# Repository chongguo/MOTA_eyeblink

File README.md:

# MOTA_eyeblink
Here are the design files and code for a custom eye blink conditioning system.

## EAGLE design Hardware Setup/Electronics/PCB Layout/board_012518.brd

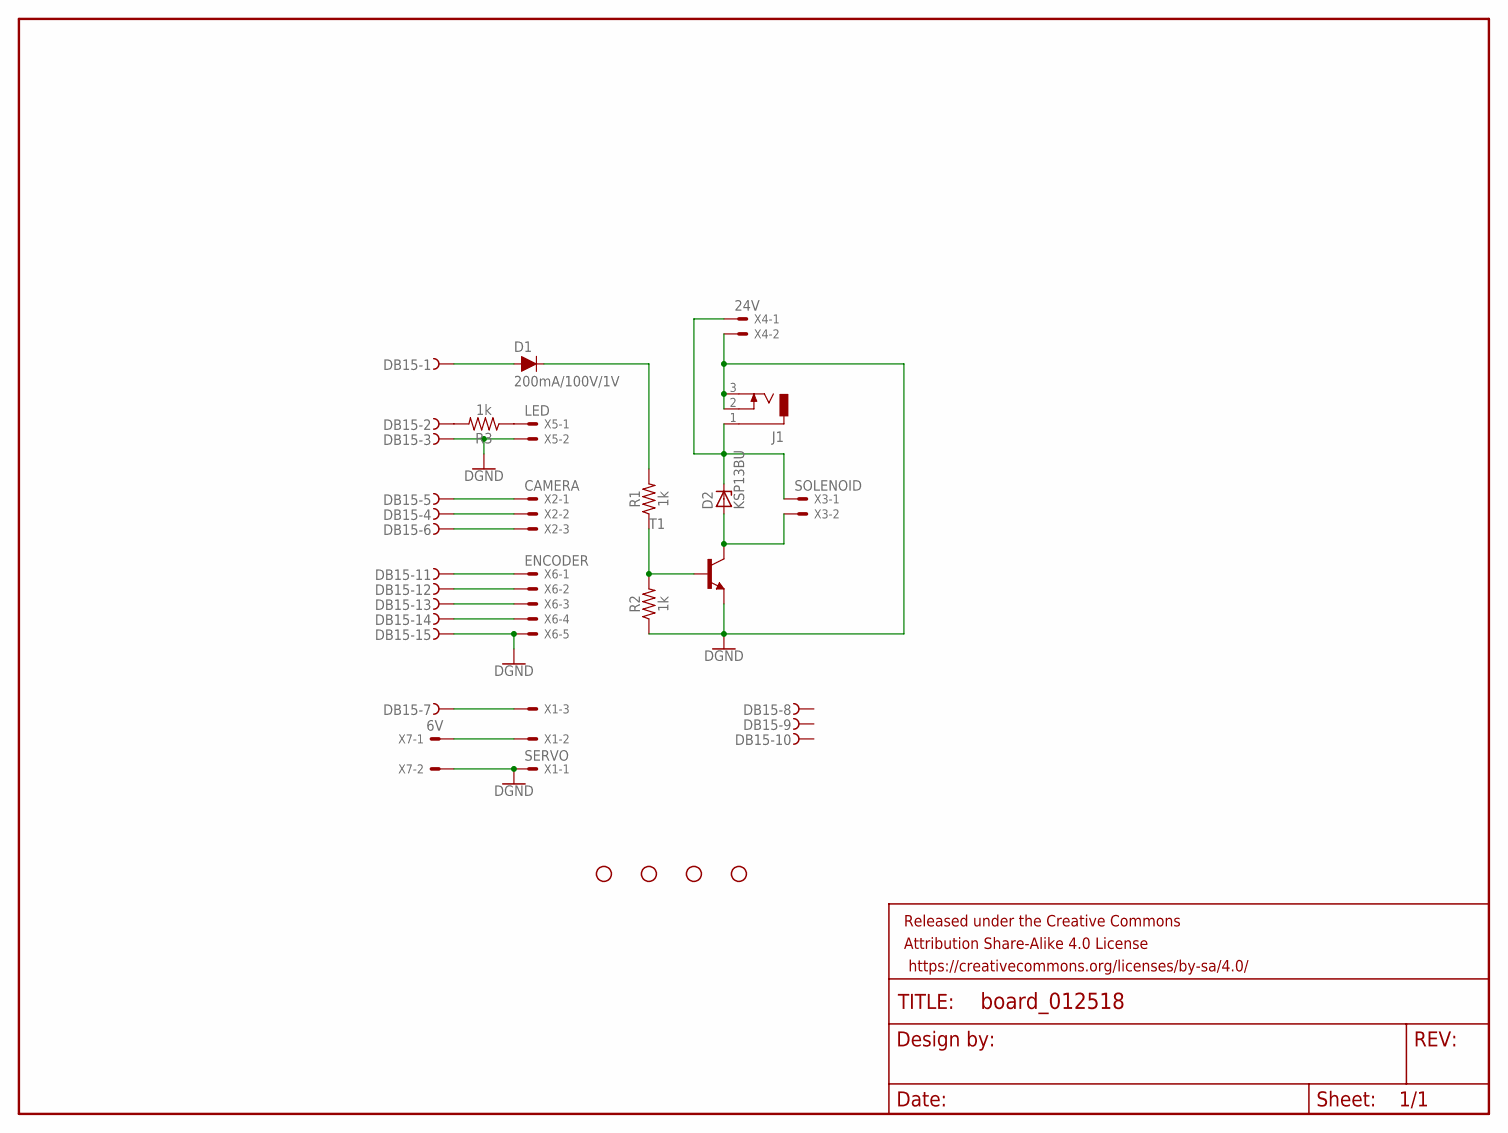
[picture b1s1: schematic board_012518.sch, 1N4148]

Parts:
D1: 200mA/100V/1V; DIODE-1N4148
D2: KSP13BU; P1Z12
DB15: D-SUB15-HDR15RA; HDR15RA
FRAME1: FRAME-LETTER; CREATIVE_COMMONS
H1, H2, H3, H4: STAND-OFF
J1: DCJ0303
R1, R2, R3: 1k; AXIAL-0.3
T1: MPSA13-NPN-TO92-EBC; TO92-EBC
X1: SERVO; 70553-03
X2: CAMERA; 70553-03
X3: SOLENOID; 70553-02
X4: 24V; 70553-02
X5: LED; 70553-02
X6: ENCODER; 70553-05
X7: 6V; 70553-02

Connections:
GND: DB15.3, DB15.15, J1.2, J1.3, R2.P$1 (1), T1.E, X1.1, X4.2, X5.2, X6.5, X7.2
unnamed: R1.P$1 (1), R2.P$2 (2), T1.B
unnamed: D1.C, R1.P$2 (2)
unnamed: D1.A, DB15.1
unnamed: D2.A, T1.C, X3.2
unnamed: D2.C, J1.1, X3.1, X4.1
unnamed: X1.2, X7.1
unnamed: R3.P$1 (1), X5.1
unnamed: DB15.11, X6.1
unnamed: DB15.12, X6.2
unnamed: DB15.4, X2.2
unnamed: DB15.13, X6.3
unnamed: DB15.2, R3.P$2 (2)
unnamed: DB15.14, X6.4
unnamed: DB15.5, X2.1
unnamed: DB15.6, X2.3
unnamed: DB15.7, X1.3

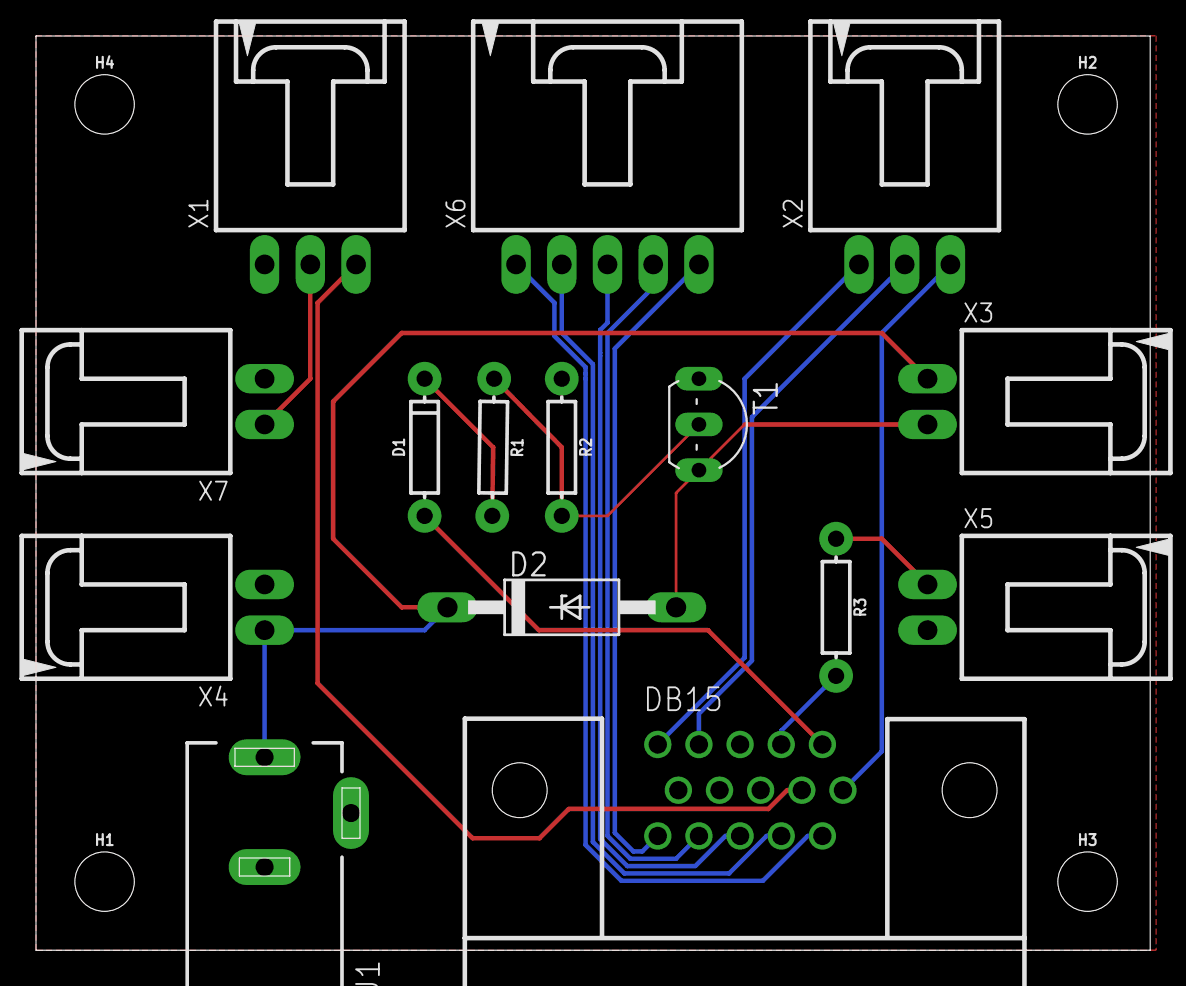
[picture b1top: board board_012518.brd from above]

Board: 2 copper layers, 61.9 x 50.8 mm, 20 parts (0 on the bottom side), 17 nets.

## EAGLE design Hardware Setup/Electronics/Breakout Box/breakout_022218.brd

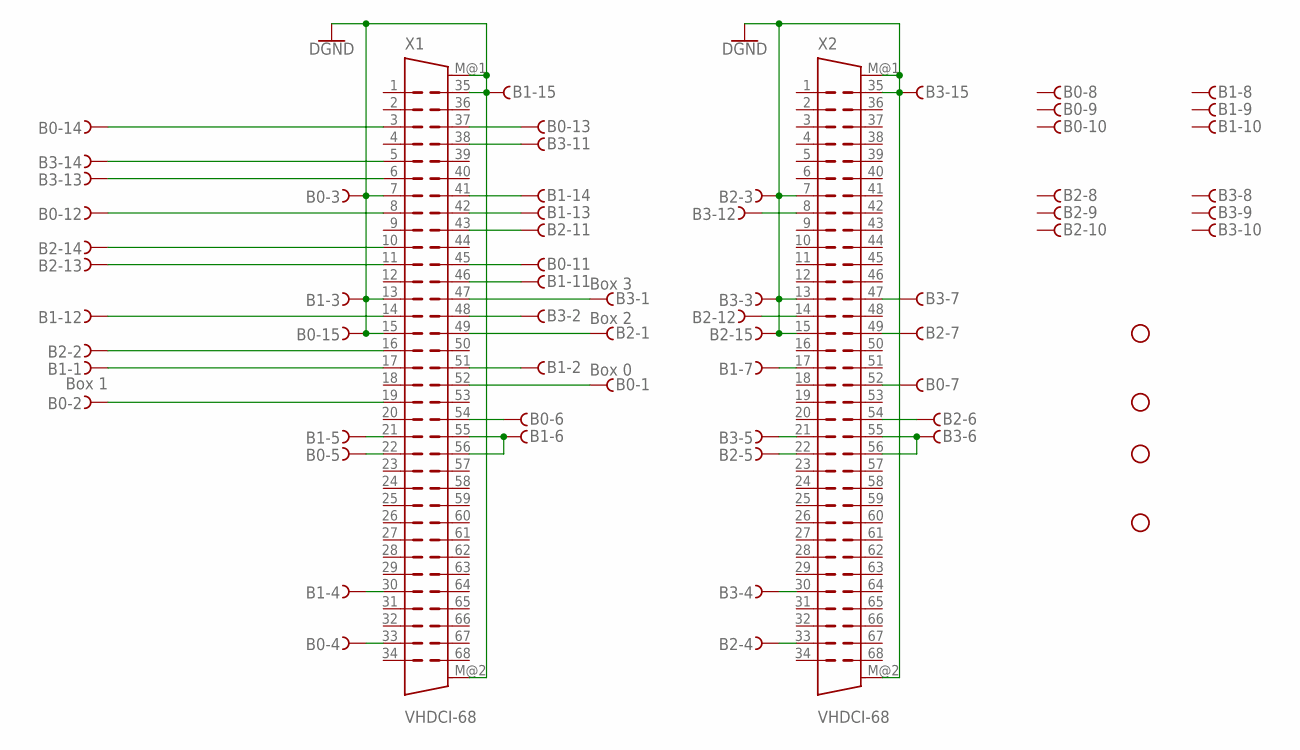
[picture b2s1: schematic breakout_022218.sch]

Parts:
B0: Box 0; HDR15RA
B1: Box 1; HDR15RA
B2: Box 2; HDR15RA
B3: Box 3; HDR15RA
H1, H2, H3, H4: STAND-OFF
X1, X2: VHDCI-68

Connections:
GND: B0.3, B0.15, B1.3, B1.15, B2.3, B2.15, B3.3, B3.15, X1.7, X1.13, X1.15, X1.35, X1.M@1 (S), X1.M@2 (S), X2.7, X2.13, X2.15, X2.35, X2.M@1 (S), X2.M@2 (S)
unnamed: B0.6, X1.54
unnamed: B1.6, X1.55, X1.56
unnamed: B2.6, X2.54
unnamed: B3.6, X2.55, X2.56
unnamed: B0.5, X1.22
unnamed: B1.5, X1.21
unnamed: B2.5, X2.22
unnamed: B3.5, X2.21
unnamed: B0.4, X1.33
unnamed: B1.4, X1.30
unnamed: B2.4, X2.33
unnamed: B3.4, X2.30
unnamed: B0.1, X1.52
unnamed: B1.1, X1.17
unnamed: B2.1, X1.49
unnamed: B3.1, X1.47
unnamed: B0.2, X1.19
unnamed: B1.2, X1.51
unnamed: B2.2, X1.16
unnamed: B3.2, X1.48
unnamed: B3.12, X2.8
unnamed: B2.12, X2.14
unnamed: B0.7, X2.52
unnamed: B1.7, X2.17
unnamed: B2.7, X2.49
unnamed: B3.7, X2.47
unnamed: B0.12, X1.8
unnamed: B1.12, X1.14
unnamed: B0.11, X1.45
unnamed: B1.11, X1.46
unnamed: B2.11, X1.43
unnamed: B3.11, X1.38
unnamed: B0.13, X1.37
unnamed: B1.13, X1.42
unnamed: B2.13, X1.11
unnamed: B3.13, X1.6
unnamed: B0.14, X1.3
unnamed: B1.14, X1.41
unnamed: B2.14, X1.10
unnamed: B3.14, X1.5

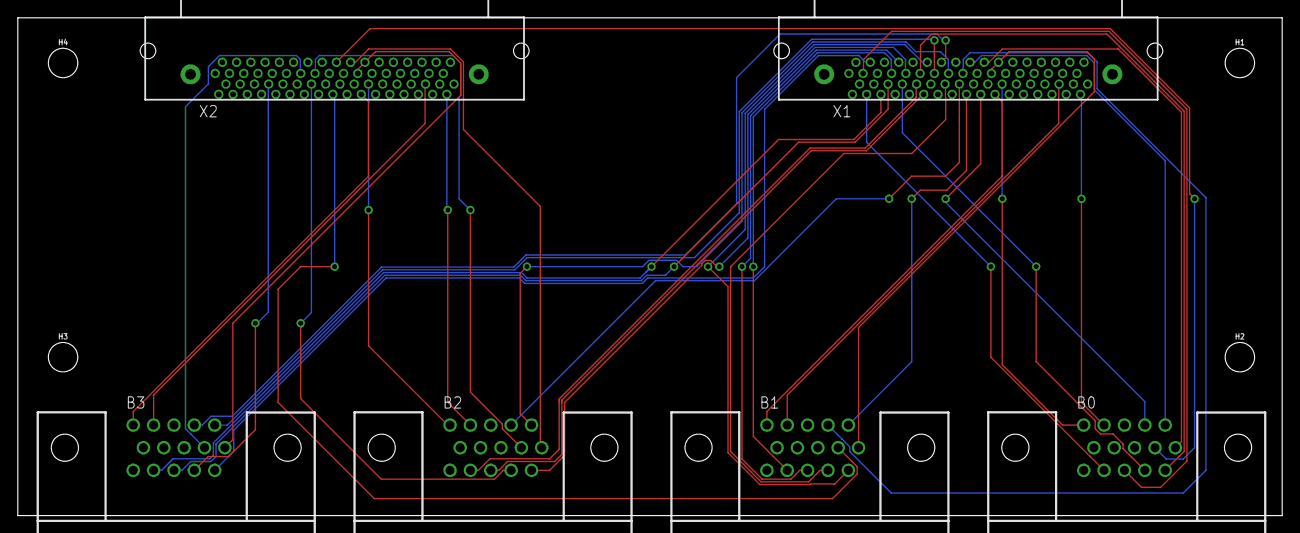
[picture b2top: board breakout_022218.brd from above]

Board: 2 copper layers, 141.9 x 55.9 mm, 10 parts (0 on the bottom side), 41 nets.

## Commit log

2019-02-07 added Hardware setups

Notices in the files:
parts and their libraries:
SparkFun-Hardware: Licensing: Creative Commons ShareAlike 4.0 International - https://creativecommons.org/licenses/by-sa/4.0
SparkFun-Aesthetics: Released under the Creative Commons Attribution Share-Alike 4.0 License
SparkFun-Aesthetics: https://creativecommons.org/licenses/by-sa/4.0
